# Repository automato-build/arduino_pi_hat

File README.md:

# arduino_pi_serial HAT

#### TOP VIEW

#### BOTTOM VIEW

**Note:** _This is  part of a bigger project with automato.farm. This is just a small testing unit for some initial steps for next bigger ideas_

Assuming you are using [latest raspbian lite terminal only image](http://downloads.raspberrypi.org/raspbian/release_notes.txt) 
(we do not need GUI crap ATM).
Also assuming you have **updated**, **upgraded** and **set your locales** from the `raspi-config`. 

### CONFIGURE HARDWRAE SERIAL INTERFACE:
In `raspi-config`, under `interfaces` option **disbale console over serial** and then select **enable hardware serial**.

`sudo reboot`

Then run

`sudo ./setup_script.sh`

This sets fixes some setup

### A BIT ABOUT THE HARDWARE:
We are suing foot print of [Arduino Pro mini 3.3 V 8mHz](https://cdn.sparkfun.com/datasheets/Dev/Arduino/Boards/Arduino-Pro-Mini-v14.pdf) for the HAT in the schematic as PI's logic levels are all 3.3V. 

We are also providing some external 5 Volt supply for which we have created some back current 
and voltage surge protection circuit following the guidelines of Raspvbberry pi HAT [design guides](https://github.com/raspberrypi/hats/blob/master/designguide.md)

Also we have provided some Breakout GPIO pins for both Arduino and PI. (**Note**: _Not all the pins are broken out.You mighht need to solder few wires._)

We have also broken out ISP Ports for burning bootloader to ATMEga328. 
PLease [follow this guide](http://www.electronoobs.com/eng_arduino_tut6.php) here on how to do so. 
Only keep in mind few thing:
1. Use another Arduino Pro mini 3.3 V 8MHz as ISP programmer (folow the guide above on how to prepapre an Arduino for burning bootloader). Also use a 3.3 V logic enabled FTDI board for this master pro mini as pro minis do not have USB interface like pro micros. Don't forget to enable 3.3 V logic on it. Most boards have a jumper to switch between logic levels)

2. Also connect the ISP ports from this board (Will be marked on the baord) to the _MOSI_, _MISO_, _SCK_ and _CS_ pins of the programmer Arduino Pro mini. Rest follow the guide of burning bootloader.
3. Then you can use the same FTDI programmer  with the programming pads on the board to upload your code to the ATmega328.

In the design we have connected _PI's RX_ to Arduino's digital _pin 3_ and _PI's TX_ to Arduino's digital _pin 2_. We would be using **"SoftwareSerial"** lib on Arduino's side to confifure those pins as _software serial pins_ to establish serial communication with PI. This way we can keep the FTDI programmer attached to the programming pads on the baord to use Arduino's default Serial port for debugging the ATMega328.

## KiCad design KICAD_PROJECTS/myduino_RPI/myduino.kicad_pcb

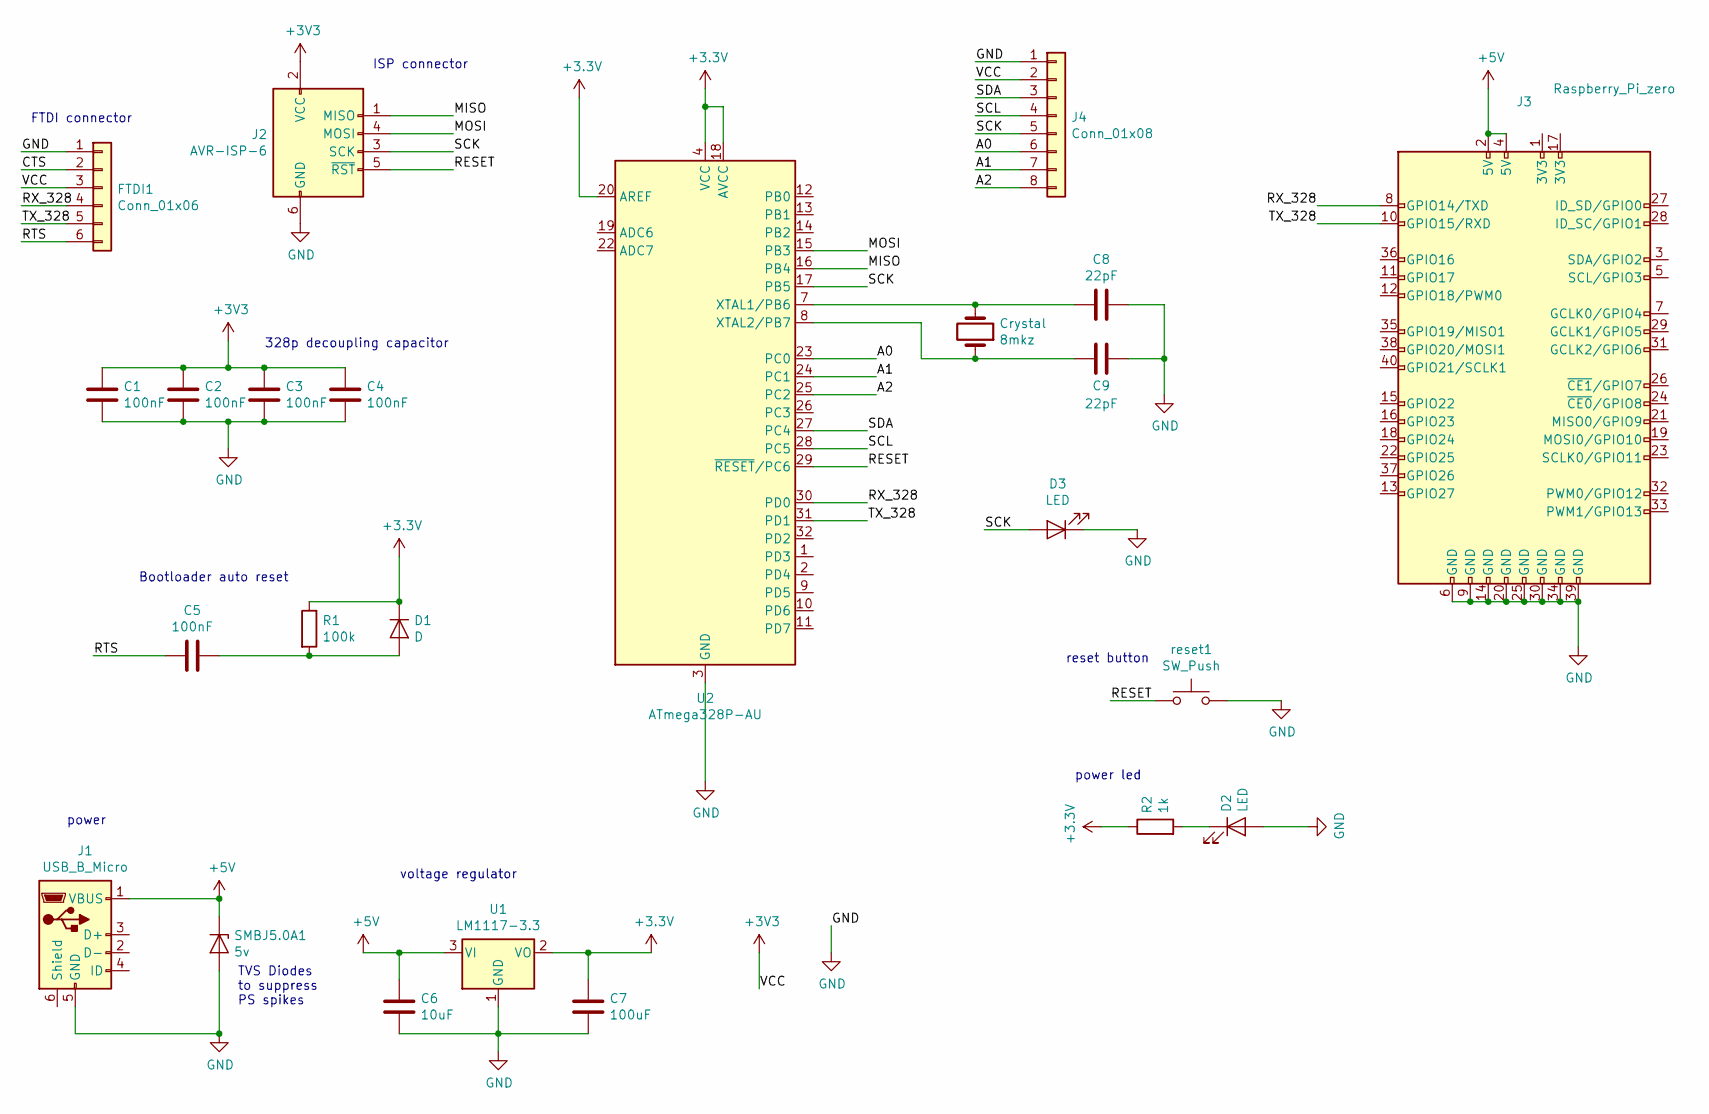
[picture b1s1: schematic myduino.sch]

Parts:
C1, C2, C3, C4, C5: 100nF; C_0805_2012Metric_Pad1.15x1.40mm_HandSolder
C6: 10uF; C_0805_2012Metric_Pad1.15x1.40mm_HandSolder
C7: 100uF; C_Elec_6.3x5.4
C8, C9: 22pF; C_0805_2012Metric_Pad1.15x1.40mm_HandSolder
Crystal: 8mkz; Crystal_SMD_HC49-SD
D1: D; D_0805_2012Metric
D2, D3: LED; LED_0805_2012Metric_Pad1.15x1.40mm_HandSolder
FTDI1: Conn_01x06; PinSocket_1x06_P2.54mm_Vertical
J1: USB_B_Micro; USB_Micro-B_Wuerth_629105150521_CircularHoles
J2: AVR-ISP-6; PinHeader_2x03_P2.54mm_Vertical
J3: Raspberry_Pi_zero; PinHeader_2x20_P2.54mm_Vertical_SMD
J4: Conn_01x08; PinSocket_1x08_P2.54mm_Vertical
R1: 100k; R_0805_2012Metric_Pad1.15x1.40mm_HandSolder
R2: 1k; R_0805_2012Metric_Pad1.15x1.40mm_HandSolder
SMBJ5.0A1: 5v; D_SMB
U1: LM1117-3.3; SOT-223-3_TabPin2
U2: ATmega328P-AU; TQFP-32_7x7mm_P0.8mm
reset1: SW_Push; SW_SPST_PTS645

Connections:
+5V: C6.1, J1.1 (VBUS), J3.2 (5V), J3.4 (5V), SMBJ5.0A1.1 (K), U1.3 (VI)
/A0: J4.6, U2.23 (PC0)
/A1: J4.7, U2.24 (PC1)
/A2: J4.8, U2.25 (PC2)
/CTS: FTDI1.2
/MISO: J2.1 (MISO), U2.16 (PB4)
/MOSI: J2.4 (MOSI), U2.15 (PB3)
/RESET: J2.5 (~RST), U2.29 (~RESET~/PC6), reset1.1
/RTS: C5.2, FTDI1.6; also elsewhere on the board
/RX_328: FTDI1.4, J3.8 (GPIO14/TXD), U2.30 (PD0)
/SCK: D3.2 (A), J2.3 (SCK), J4.5, U2.17 (PB5)
/SCL: J4.4, U2.28 (PC5)
/SDA: J4.3, U2.27 (PC4)
/TX_328: FTDI1.5, J3.10 (GPIO15/RXD), U2.31 (PD1)
GND: C1.2, C2.2, C3.2, C4.2, C6.2, C7.2, C8.1, C9.1, D2.2 (A), D3.1 (K), FTDI1.1, J1.5 (GND), J2.6 (GND), J3.6 (GND), J3.9 (GND), J3.14 (GND), J3.20 (GND), J3.25 (GND), J3.30 (GND), J3.34 (GND), J3.39 (GND), J4.1, SMBJ5.0A1.2 (A), U1.1 (GND), U2.3 (GND), U2.5 (GND), U2.21 (GND), reset1.2
unnamed: C5.1, D1.2 (A), R1.2
unnamed 17: C8.2, Crystal.2, U2.7 (XTAL1/PB6); also elsewhere on the board
unnamed 18: C9.2, Crystal.1, U2.8 (XTAL2/PB7); also elsewhere on the board
unnamed: D2.1 (K), R2.2

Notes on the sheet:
328p decoupling capacitor
reset button
Bootloader auto reset
ISP connector
power
voltage regulator
FTDI connector
power led
TVS Diodes to suppress PS spikes

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
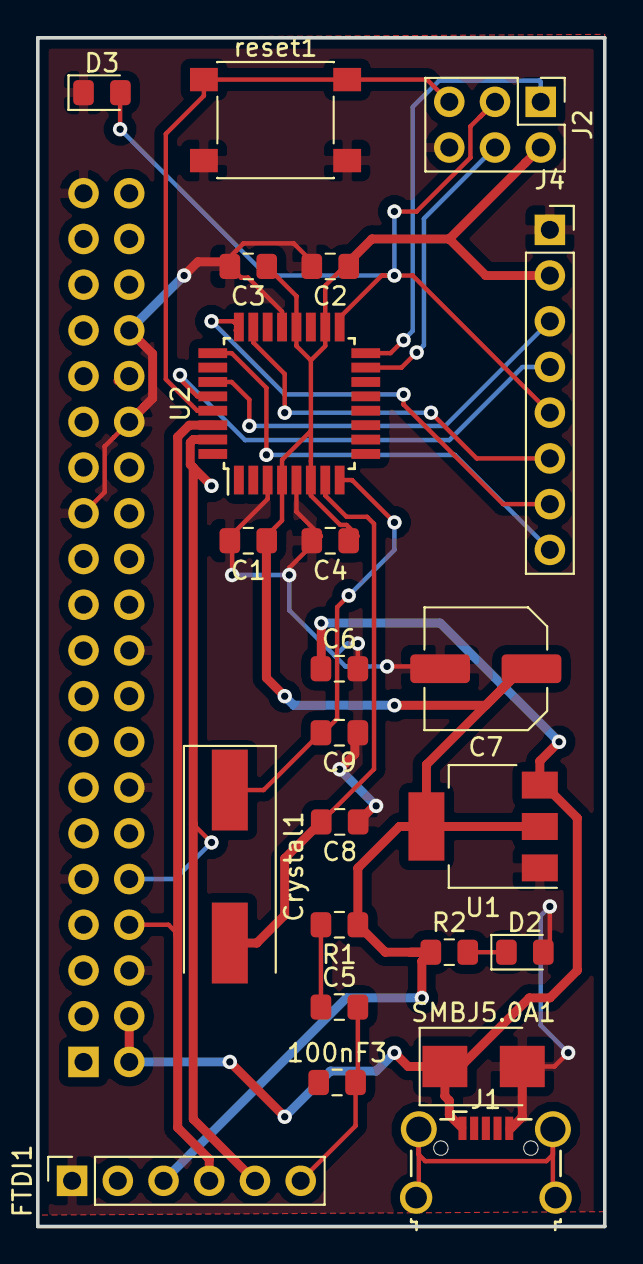
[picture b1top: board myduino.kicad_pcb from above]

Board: 2 copper layers, 31.5 x 66.0 mm, 24 parts (1 on the bottom side), 19 nets.

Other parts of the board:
100nF3: C; C_0805_2012Metric_Pad1.15x1.40mm_HandSolder
Crystal1: 8mkz; Crystal_SMD_HC49-SD

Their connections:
/RTS: 100nF3.2; also elsewhere on the board
unnamed 17: Crystal1.2; also elsewhere on the board
unnamed 18: Crystal1.1; also elsewhere on the board

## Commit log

2019-02-20 added sample raspi side python serail scripts
2019-02-20 added a install script
2019-02-20 created README
2019-02-20 updating content in readme
2019-02-20 updating content of README
2019-02-20 updating readme
2019-02-20 sargagg
2019-02-20 sdrrfwert
2019-02-20 updating the README
2019-02-20 PCB's images
2019-02-20 added images
2019-02-21 checkiong migration to new profile
2019-02-21 added a jumper to separate ext voltage for testing it the volt reg citcuit doesn't work
2019-02-21 removed junk .test
2019-02-21 up-dated read me with new preview image including the new voltage separation jumper
2019-03-09 add lorenzo's pihat design
